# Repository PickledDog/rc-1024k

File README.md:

# rc-1024k
 512K+512K RAM/ROM card for RC2014

## Overview
This RC2014-compatible board provides RAM and flash ROM, software-pageable in 32k pages. 16 ROM and 16 RAM pages may be paged into the lower 32k of Z80 memory. This paging scheme is compatible with Wayne Warthen's [RomWBW](https://github.com/wwarthen/RomWBW).

## Memory details
For ROM, a SST39SF040 512k x 8 flash chip is used. It can be programmed in-place using Will Sowerbutts' FLASH4 utility (included with RomWBW). For RAM, an AS6C4008 512k x 8 SRAM is used, providing 512K of addressable memory. Both are divided into 32k pages, and any page of either chip can be paged into the lower 32k of the address space. The upper 32k is permanently mapped to the last page of the RAM chip.

## Paging
Upon reset, the first page of the ROM is mapped to the lower 32k. If left alone, the board will behave like any 32k ROM+32k RAM RC2014 system. A config register is used to set the currently mapped page, presented as an I/O device at 0x78 (the address used by most "large" Z80 memory systems). The low nibble sets the page number (0-15), and high bit 7 selects the chip (0 for ROM, 1 for RAM).

The port address and layout are chosen to be (mostly) compatible with the [RetroBrew SBC](https://www.retrobrewcomputers.org/doku.php?id=boards:sbc:sbc_v2:sbc_v2-003). The SBC has separate ROM and RAM registers (on 0x78 and 0x7C); this board uses a single register for both, which can be written to from either address.

## Firmware
Many [RC2014 ROM images](https://github.com/RC2014Z80/RC2014/tree/master/ROMs) can be used (selecting the right image for your serial board), but some will require modification to accommodate the different paging system. The 32k BASIC images work unmodified. Stephen C Cousins' excellent [Small Computer Monitor](https://smallcomputercentral.wordpress.com/small-computer-monitor/) can be used as well - choose the R3 configuration. CP/M loading *won't work* without code changes.

But most importantly, this board is compatible with [RomWBW](https://github.com/wwarthen/RomWBW), providing several CP/M versions, ROM applications, and maximized free application memory. It will need to be built from source with configuration changes, although this is fairly straightforward (RomWBW includes its entire build toolchain in the source tree). The build process is covered in [this page](https://github.com/wwarthen/RomWBW/blob/master/Source/ReadMe.txt) from the RomWBW documentation (including Linux and Mac instructions). An example image can be found in the [firmware](/firmware) directory.

### RomWBW Config changes
With the [source tree](https://github.com/wwarthen/RomWBW) unpacked, go into `Source/HBIOS/Config` and make a copy of `RCZ80_std.asm` (call it `RCZ80_pd.asm`). Edit this new file, and add the following lines:
```
MEMMGR		.SET	MM_SBC		; MEMORY MANAGER: MM_[SBC|Z2|N8|Z180]
MPCL_RAM	.EQU	$78		; SBC MEM MGR RAM PAGE SELECT REG (WRITE ONLY)
MPCL_ROM	.EQU	$7C		; SBC MEM MGR ROM PAGE SELECT REG (WRITE ONLY)
;
```
With our new file, we can go ahead and build our ROM image. Under Windows, this is done with the following commands in `Source`:

* `BuildShared`
  * Wait for this to complete, ignoring the harmless program origin warnings
* `BuildROM`
  * Enter `RCZ80` at the *Platform* prompt
  * Enter `pd` at the *Configuration* prompt

Once the build is complete, we are done! Back at the root of the source tree, go into `Binary` and retrieve our new `RCZ80_pd.rom`. This can now be burned to the flash chip using an EPROM programmer, such as a [TL866](https://www.ebay.com/sch/i.html?_nkw=tl866ii+plus).

## Part selection
Bill Of Materials and part references are below. I recommend using gold-plated header for the bus connection - I use these ones from [Pololu](https://www.pololu.com/product/967) or [Sparkfun](https://www.sparkfun.com/products/553). A nice detail of these, is that they sit at the same height as double-row header in a backplane.

The specified parts are just the ones I used, and can be substituted as needed - Mouser links provided for convenience and reference.

| Reference | Value | Qty | Mouser link |
| --------- | ----- | --- | ----------- |
| C1-C6 | 100nF ceramic | 6 | [KEMET C315C104M5U5TA](https://www.mouser.com/ProductDetail/C315C104M5U5TA7303) |
| J1 | 1x40 right-angle header | 1 | [Wurth 61304011021](https://www.mouser.com/ProductDetail/61304011021) |
| U1 | SST39SF040 NOR flash | 1 | [Microchip SST39SF040-70-4C-PHE](https://www.mouser.com/ProductDetail/SST39SF040-70-4C-PHE) |
| U2 | AS6C4008 SRAM | 1 | [Alliance AS6C4008-55PCN](https://www.mouser.com/ProductDetail/AS6C4008-55PCN) |
| | sockets | 2 | [Amphenol DILB32P-223TLF](https://www.mouser.com/ProductDetail/DILB32P-223TLF) |
| U3 | 74HCT138 | 1 | [TI SN74HCT138N](https://www.mouser.com/ProductDetail/SN74HCT138N) |
| U4 | 74HCT174 | 1 | [TI CD74HCT174E](https://www.mouser.com/ProductDetail/CD74HCT174E) |
| U5 | 74HCT32 | 1 | [TI SN74HCT32N](https://www.mouser.com/ProductDetail/SN74HCT32N) |
| U6 | 74HCT253 | 1 | [TI CD74HCT253E](https://www.mouser.com/ProductDetail/CD74HCT253E) |

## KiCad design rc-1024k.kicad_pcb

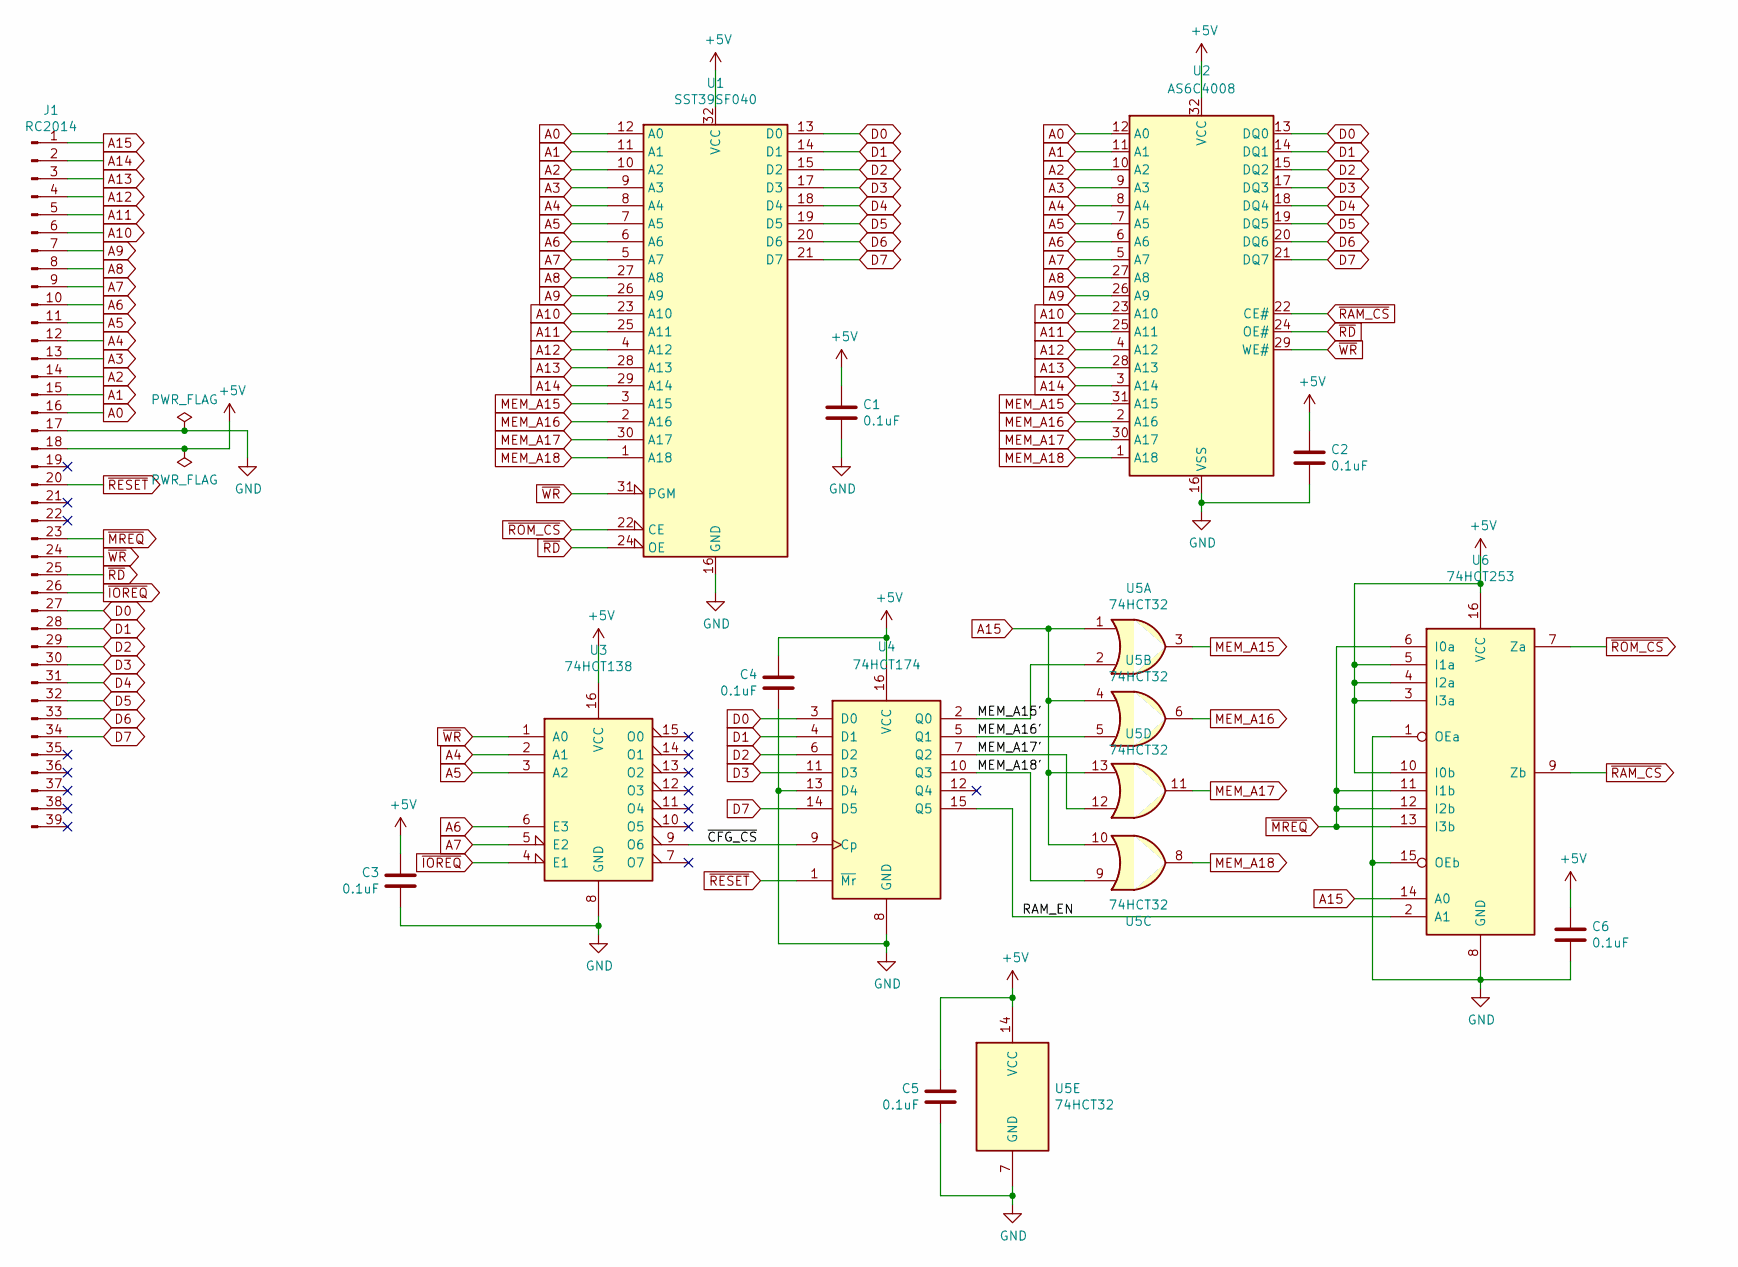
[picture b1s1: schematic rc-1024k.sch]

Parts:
C1, C2, C3, C4, C5, C6: 0.1uF; C_Disc_D3.0mm_W1.6mm_P2.50mm
J1: RC2014; PinHeader_1x39_P2.54mm_Vertical
U1: SST39SF040; DIP-32_W15.24mm_LongPads
U2: AS6C4008; DIP-32_W15.24mm_LongPads
U3: 74HCT138; DIP-16_W7.62mm_LongPads
U4: 74HCT174; DIP-16_W7.62mm_LongPads
U5: 74HCT32; DIP-14_W7.62mm_LongPads
U6: 74HCT253; DIP-16_W7.62mm_LongPads

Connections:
+5V: C1.1, C2.1, C3.2, C4.2, C5.2, C6.1, J1.18, U1.32 (VCC), U2.32 (VCC), U3.16 (VCC), U4.16 (VCC), U5.14 (VCC), U6.3 (I3a), U6.4 (I2a), U6.5 (I1a), U6.10 (I0b), U6.16 (VCC)
/MEM_A15': U4.2 (Q0), U5.2
/MEM_A16': U4.5 (Q1), U5.5
/MEM_A17': U4.7 (Q2), U5.12
/MEM_A18': U4.10 (Q3), U5.9
/RAM_EN: U4.15 (Q5), U6.2 (A1)
/~CFG_CS: U3.9 (O6), U4.9 (Cp)
A0: J1.16, U1.12 (A0), U2.12 (A0)
A1: J1.15, U1.11 (A1), U2.11 (A1)
A2: J1.14, U1.10 (A2), U2.10 (A2)
A3: J1.13, U1.9 (A3), U2.9 (A3)
A4: J1.12, U1.8 (A4), U2.8 (A4), U3.2 (A1)
A5: J1.11, U1.7 (A5), U2.7 (A5), U3.3 (A2)
A6: J1.10, U1.6 (A6), U2.6 (A6), U3.6 (E3)
A7: J1.9, U1.5 (A7), U2.5 (A7), U3.5 (E2)
A8: J1.8, U1.27 (A8), U2.27 (A8)
A9: J1.7, U1.26 (A9), U2.26 (A9)
A10: J1.6, U1.23 (A10), U2.23 (A10)
A11: J1.5, U1.25 (A11), U2.25 (A11)
A12: J1.4, U1.4 (A12), U2.4 (A12)
A13: J1.3, U1.28 (A13), U2.28 (A13)
A14: J1.2, U1.29 (A14), U2.3 (A14)
A15: J1.1, U5.1, U5.4, U5.10, U5.13, U6.14 (A0)
D0: J1.27, U1.13 (D0), U2.13 (DQ0), U4.3 (D0)
D1: J1.28, U1.14 (D1), U2.14 (DQ1), U4.4 (D1)
D2: J1.29, U1.15 (D2), U2.15 (DQ2), U4.6 (D2)
D3: J1.30, U1.17 (D3), U2.17 (DQ3), U4.11 (D3)
D4: J1.31, U1.18 (D4), U2.18 (DQ4)
D5: J1.32, U1.19 (D5), U2.19 (DQ5)
D6: J1.33, U1.20 (D6), U2.20 (DQ6)
D7: J1.34, U1.21 (D7), U2.21 (DQ7), U4.14 (D5)
GND: C1.2, C2.2, C3.1, C4.1, C5.1, C6.2, J1.17, U1.16 (GND), U2.16 (VSS), U3.8 (GND), U4.8 (GND), U4.13 (D4), U5.7 (GND), U6.1 (OEa), U6.8 (GND), U6.15 (OEb)
MEM_A15: U1.3 (A15), U2.31 (A15), U5.3
MEM_A16: U1.2 (A16), U2.2 (A16), U5.6
MEM_A17: U1.30 (A17), U2.30 (A17), U5.11
MEM_A18: U1.1 (A18), U2.1 (A18), U5.8
~IOREQ: J1.26, U3.4 (E1)
~MREQ: J1.23, U6.6 (I0a), U6.11 (I1b), U6.12 (I2b), U6.13 (I3b)
~RAM_CS: U2.22 (CE#), U6.9 (Zb)
~RD: J1.25, U1.24 (OE), U2.24 (OE#)
~RESET: J1.20, U4.1 (~Mr)
~ROM_CS: U1.22 (CE), U6.7 (Za)
~WR: J1.24, U1.31 (PGM), U2.29 (WE#), U3.1 (A0)

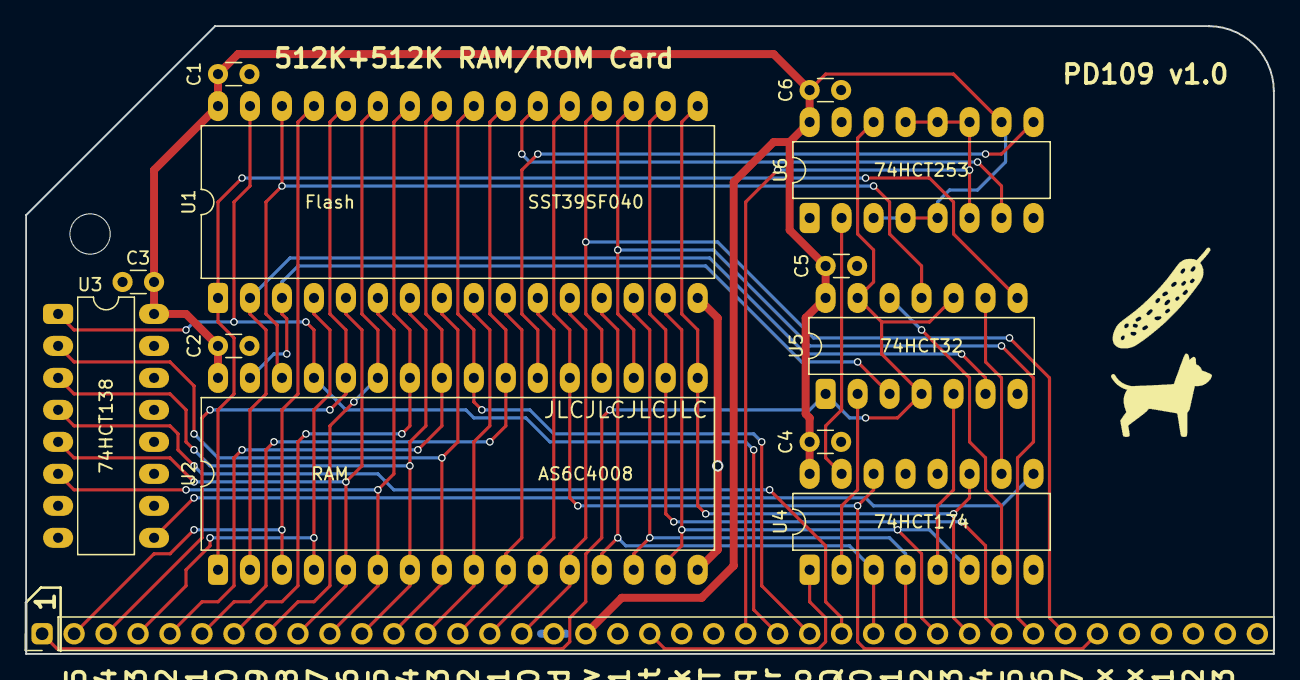
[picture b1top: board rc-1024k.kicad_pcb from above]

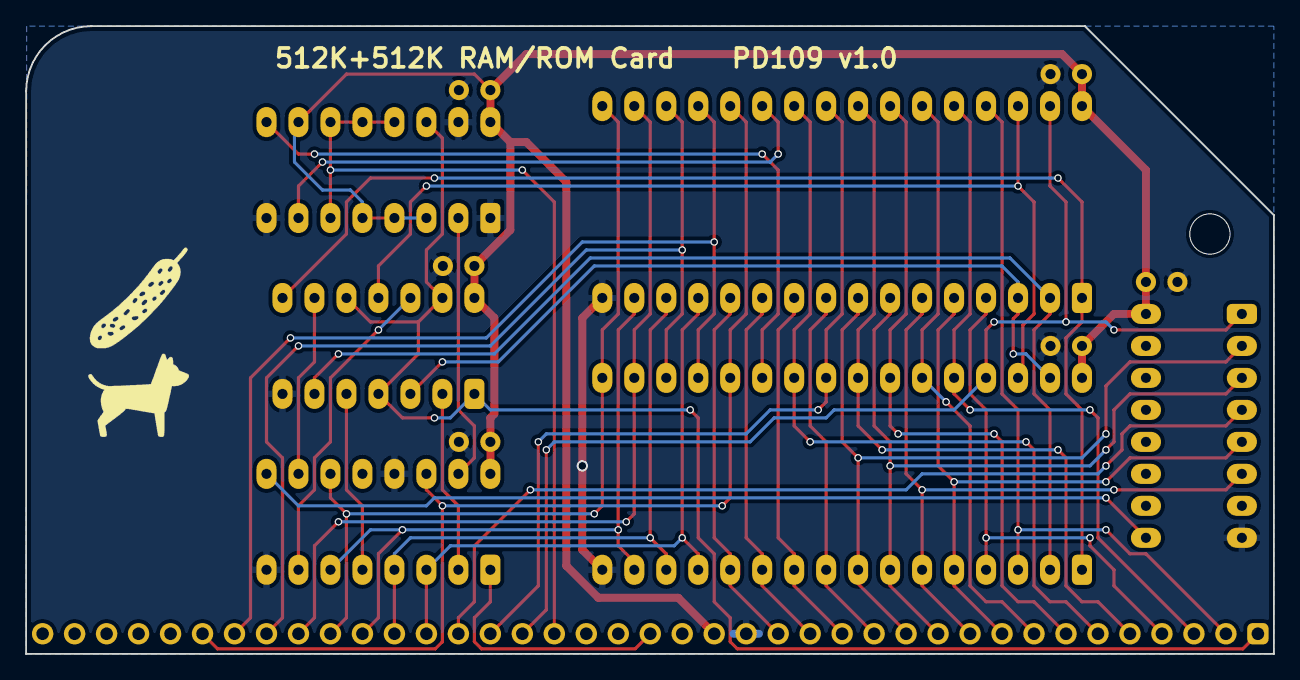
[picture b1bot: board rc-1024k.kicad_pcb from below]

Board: 2 copper layers, 99.1 x 49.9 mm, 17 parts (2 on the bottom side), 43 nets.

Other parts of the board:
Ref**: Val**; Symbol-Dog-8mm
Ref**#2: Val**; Symbol-Dog-8mm
Ref**#3, Ref**#4: Val**; Symbol-Pickle-8mm

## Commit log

2021-03-31 Initial commit of rc-1024k/PD109
2021-03-31 Whoops missing close paren
2021-04-02 Minor layout tweaks
2021-04-05 Rerouted datalines
2021-04-06 Add icons
2021-04-18 Add board pic
2021-04-20 Add example firmware
